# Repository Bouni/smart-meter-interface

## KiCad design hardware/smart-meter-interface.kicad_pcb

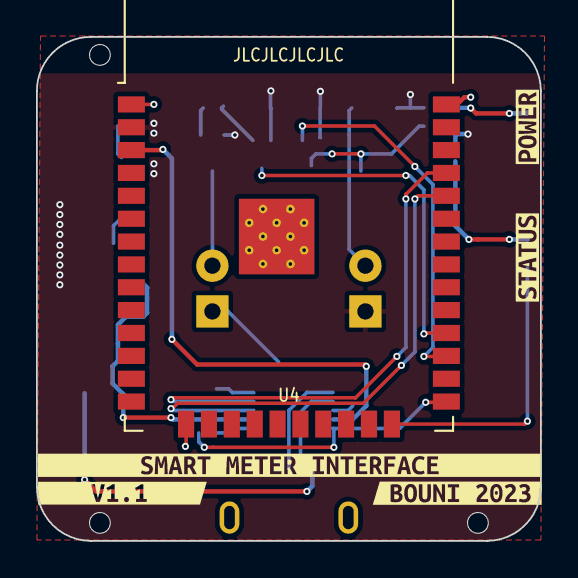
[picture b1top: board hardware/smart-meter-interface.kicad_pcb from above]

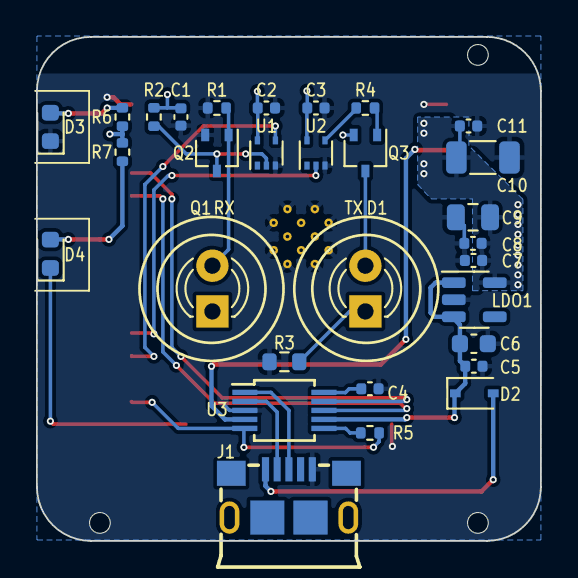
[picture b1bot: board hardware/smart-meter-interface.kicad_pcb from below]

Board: 2 copper layers, 28.0 x 28.0 mm, 39 parts (30 on the bottom side), 23 nets.

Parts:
C1, C2, C3, C5, C8, C11: 1uF; C_0402_1005Metric
C4, C7: 0.1uF; C_0402_1005Metric
C6: 10uF; C_0603_1608Metric
C9: 47uF; C_0805_2012Metric
C10: 100uF; C_1206_3216Metric
D1: SFH4356P; LED_D3.0mm_IRBlack
D2: 1N5819WS; D_SOD-323
D3: LED_G; LED_0603_1608Metric
D4: LED_B; LED_0603_1608Metric
J1: USB_B_Micro; MICRO-USB-SMD_10118193-0001LF
LDO1: ME6211C33M5G-N; SOT-23-5
Q1: SFH309; LED_D3.0mm_Clear
Q2: BC817W; SOT-323_SC-70
Q3: BC807W; SOT-323_SC-70
R1, R2, R4: 13K; R_0402_1005Metric
R3: 180; R_0603_1608Metric
R5: 4K7; R_0402_1005Metric
R6, R7: 1k; R_0402_1005Metric
TH: ToolingHole
TH#2, TH#3: ToolingHole
U1, U2: 74LVC1G17; SOT-553
U3: CH340X; MSOP-10_3x3mm_P0.5mm
U4: ESP32-WROOM-32
kibuzzard-651E74F7: G***; kibuzzard-651E74F7
kibuzzard-651E7500: G***; kibuzzard-651E7500
kibuzzard-651FCF74: G***; kibuzzard-651FCF74
kibuzzard-651FCFB8: G***; kibuzzard-651FCFB8
kibuzzard-651FCFC3: G***; kibuzzard-651FCFC3

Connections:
+3V3: C1.1, C2.1, C3.1, C7.1, C8.1, C9.1, C10.1, C11.1, LDO1.5 (VOUT), Q1.1 (C), Q3.2 (E), R2.1, R6.1, R7.1, U1.5 (VCC), U2.5 (VCC), U4.2 (VDD)
+5V: C5.1, C6.1, D2.1 (K), LDO1.1 (VIN), LDO1.3 (CE), U3.7 (VCC)
/D+: J1.3 (D+), U3.1 (UD+)
/D-: J1.2 (D-), U3.2 (UD-)
BLINK: U2.2, U4.28 (IO17)
EN: U3.4 (~RTS), U4.3 (EN)
GND: C1.2, C2.2, C3.2, C4.1, C5.2, C6.2, C7.2, C8.2, C9.2, C10.2, C11.2, D3.1 (K), J1.5 (GND), LDO1.2 (VSS), Q2.2 (E), R1.2, R3.2, U1.3 (GND), U2.3 (GND), U3.3 (GND), U4.1 (GND), U4.15 (GND), U4.38 (GND), U4.39 (GND)
IO0: R5.2, U3.5 (~CTS), U4.25 (IO0)
IO2: D4.1 (K), U4.24 (IO2)
unnamed: D1.2 (A), Q3.3 (C)
unnamed: D1.1 (K), R3.1
unnamed: D2.2 (A), J1.1 (VBUS)
unnamed: D3.2 (A), R6.2
unnamed: D4.2 (A), R7.2
unnamed: Q1.2 (E), Q2.1 (B), R1.1
unnamed: Q2.3 (C), R2.2, U1.2
unnamed: Q3.1 (B), R4.1
unnamed: R4.2, U2.4
unnamed: R5.1, U3.6 (TNOW/~DTR)
unnamed: C4.2, U3.10 (V3)
RX: U1.4, U4.27 (IO16)
RXD0: U3.8 (TXD), U4.34 (RXD0/IO3)
TXD0: U3.9 (RXD), U4.35 (TXD0/IO1)

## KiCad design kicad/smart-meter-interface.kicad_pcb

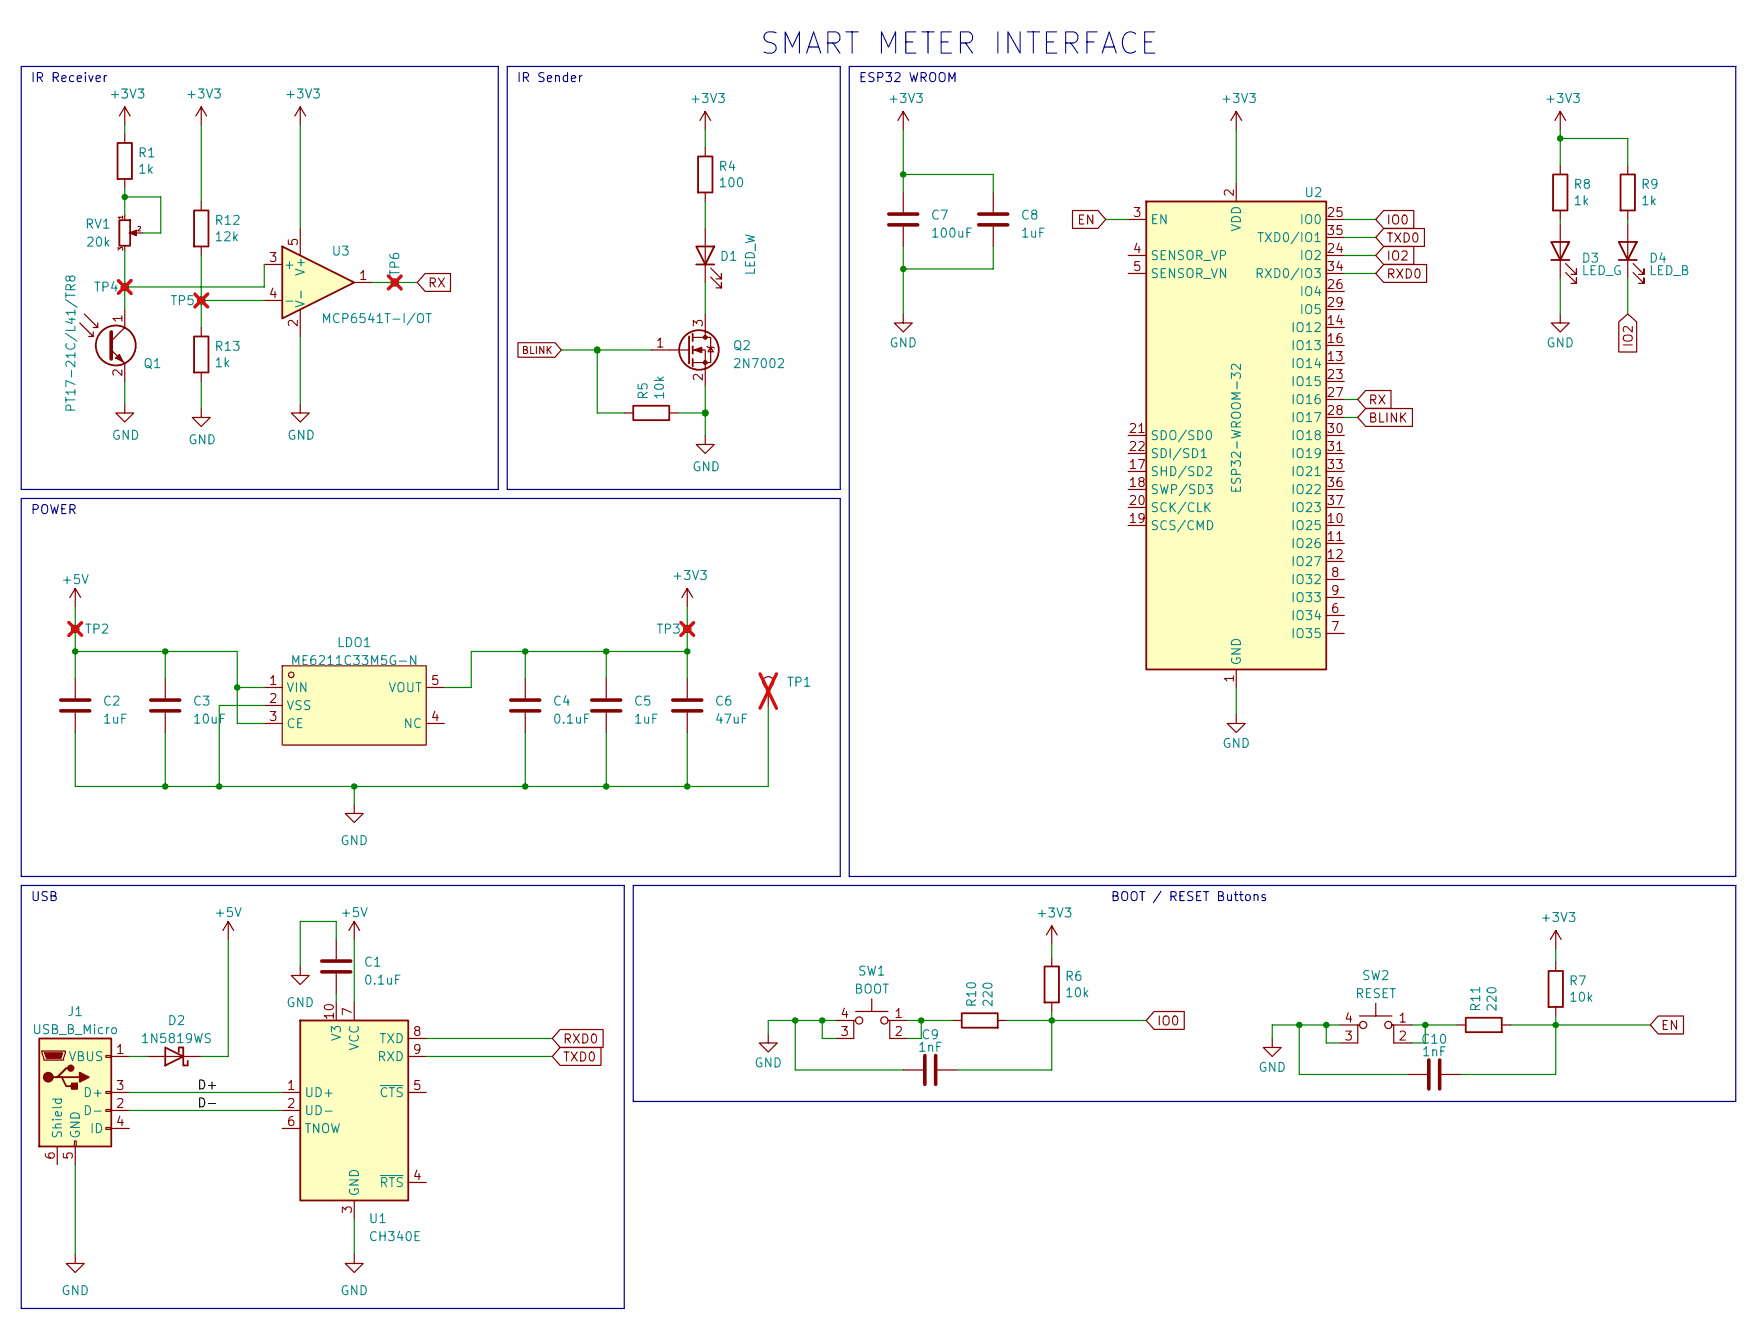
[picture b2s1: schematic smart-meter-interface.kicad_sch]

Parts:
C1, C4: 0.1uF; C_0402_1005Metric; LCSC C307331
C2, C5, C8: 1uF; C_0402_1005Metric; LCSC C52923
C3: 10uF; C_0603_1608Metric; LCSC C96446
C6: 47uF; C_0805_2012Metric; LCSC C16780
C7: 100uF; C_1206_3216Metric; LCSC C15008
C9, C10: 1nF; C_0402_1005Metric; LCSC C1523
D1: LED_W; LED_0805_2012Metric; LCSC C34499
D2: 1N5819WS; D_SOD-323; LCSC C191023
D3: LED_G; LED_0603_1608Metric; LCSC C72043
D4: LED_B; LED_0603_1608Metric; LCSC C72041
J1: USB_B_Micro; MICRO-USB-SMD_10118193-0001LF; LCSC C132562
LDO1: ME6211C33M5G-N; SOT-23-5_L3.0-W1.7-P0.95-LS2.8-BR; LCSC C82942
Q1: PT17-21C/L41/TR8; OPTO-SMD_L2.0-W1.3-R-FD; LCSC C100090
Q2: 2N7002; SOT-23; LCSC C8545
R1, R8, R9, R13: 1k; R_0402_1005Metric; LCSC C11702
R4: 100; R_0402_1005Metric; LCSC C25076
R5, R6, R7: 10k; R_0402_1005Metric; LCSC C25744
R10, R11: 220; R_0402_1005Metric; LCSC C25091
R12: 12k; R_0402_1005Metric; LCSC C25752
RV1: 20k; RES-ADJ-SMD_3P-L3.8-W3.0-P2.00-BL-FS; LCSC C128550
SW1: BOOT; SW-SMD_4P-L5.1-W5.1-P3.70-LS6.5-TL-2; LCSC C318884
SW2: RESET; SW-SMD_4P-L5.1-W5.1-P3.70-LS6.5-TL-2; LCSC C318884
TP1: TestPoint; TestPoint_Keystone_5000-5004_Miniature; not fitted
TP2, TP3, TP4, TP5, TP6: TestPoint_Small; TestPoint_Pad_D1.0mm; not fitted
U1: CH340E; MSOP-10_3x3mm_P0.5mm; LCSC C99652
U2: ESP32-WROOM-32
U3: MCP6541T-I/OT; SOT-23-5; LCSC C80839

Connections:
+3V3: C4.1, C5.1, C6.1, C7.1, C8.1, LDO1.5 (VOUT), R1.1, R4.1, R6.1, R7.1, R8.1, R9.1, R12.1, TP3.1, U2.2 (VDD), U3.5 (V+)
+5V: C2.1, C3.1, D2.1 (K), LDO1.1 (VIN), LDO1.3 (CE), TP2.1, U1.7 (VCC)
/D+: J1.3 (D+), U1.1 (UD+)
/D-: J1.2 (D-), U1.2 (UD-)
BLINK: Q2.1 (G), R5.1, U2.28 (IO17)
EN: C10.2, R7.2, R11.2, U2.3 (EN)
GND: C1.1, C2.2, C3.2, C4.2, C5.2, C6.2, C7.2, C8.2, C9.1, C10.1, D3.1 (K), J1.5 (GND), LDO1.2 (VSS), Q1.2 (E), Q2.2 (S), R5.2, R13.2, SW1.3 (K), SW1.4 (A), SW2.3 (K), SW2.4 (A), TP1.1, U1.3 (GND), U2.1 (GND), U2.15 (GND), U2.38 (GND), U2.39 (GND), U3.2 (V-)
IO0: C9.2, R6.2, R10.2, U2.25 (IO0)
IO2: D4.1 (K), U2.24 (IO2)
unnamed: D1.2 (A), R4.2
unnamed: D1.1 (K), Q2.3 (D)
unnamed: D2.2 (A), J1.1 (VBUS)
unnamed: D3.2 (A), R8.2
unnamed: D4.2 (A), R9.2
unnamed: Q1.1 (C), RV1.3, TP4.1, U3.3 (+)
unnamed: R1.2, RV1.1, RV1.2
unnamed: R10.1, SW1.1, SW1.2
unnamed: R11.1, SW2.1, SW2.2
unnamed: C1.2, U1.10 (V3)
unnamed: R12.2, R13.1, TP5.1, U3.4 (-)
RX: TP6.1, U2.27 (IO16), U3.1
RXD0: U1.8 (TXD), U2.34 (RXD0/IO3)
TXD0: U1.9 (RXD), U2.35 (TXD0/IO1)

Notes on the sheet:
POWER
USB
BOOT / RESET Buttons
ESP32 WROOM
SMART METER INTERFACE
IR Sender
IR Receiver

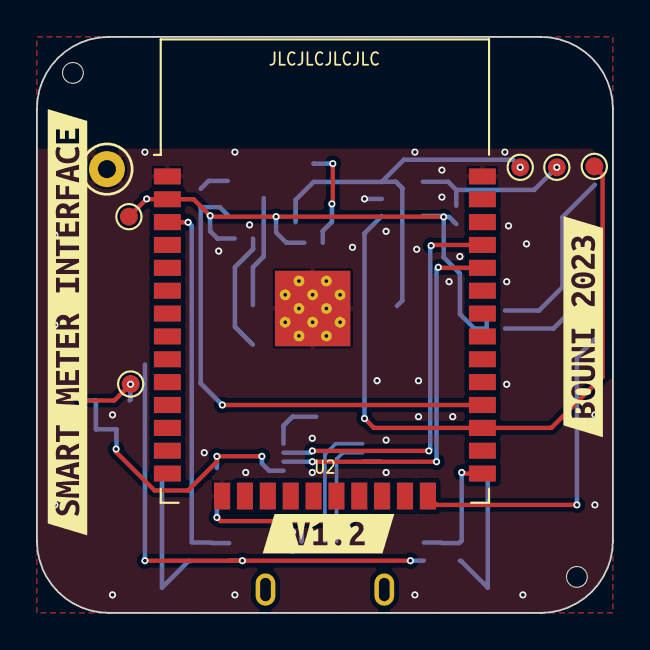
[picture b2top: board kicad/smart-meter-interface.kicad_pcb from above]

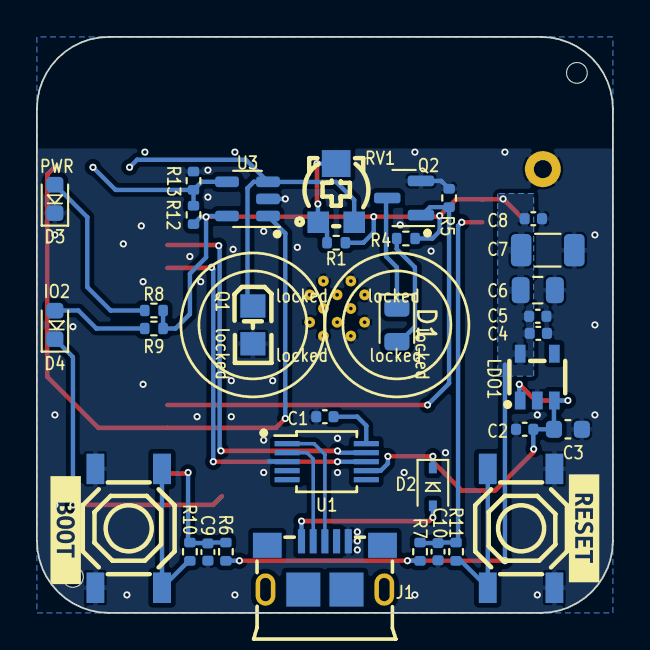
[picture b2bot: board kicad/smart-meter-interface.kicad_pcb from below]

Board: 2 copper layers, 32.0 x 32.0 mm, 48 parts (36 on the bottom side), 23 nets.

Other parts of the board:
TH1, TH2: ToolingHole
kibuzzard-63C57836: G***; kibuzzard-63C57836
kibuzzard-635BBB2F: G***; kibuzzard-635BBB2F
kibuzzard-635BBB9A: G***; kibuzzard-635BBB9A
kibuzzard-635BBBA9: G***; kibuzzard-635BBBA9
kibuzzard-64709697: G***; kibuzzard-64709697

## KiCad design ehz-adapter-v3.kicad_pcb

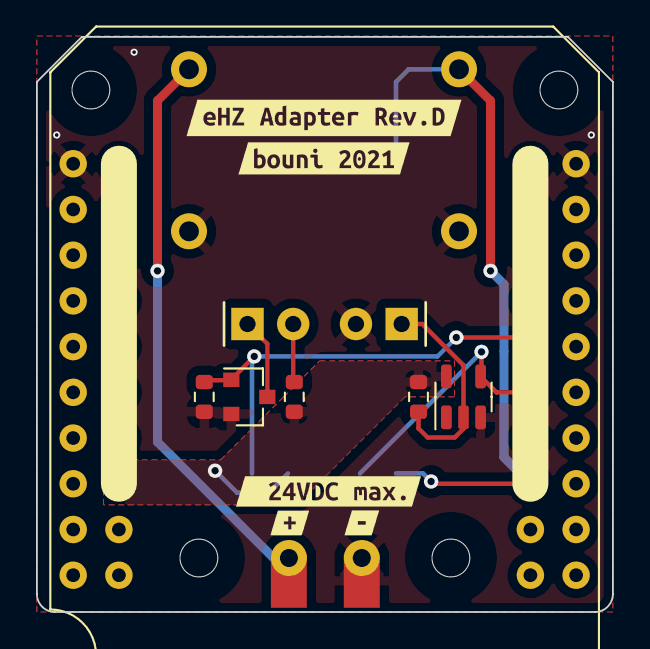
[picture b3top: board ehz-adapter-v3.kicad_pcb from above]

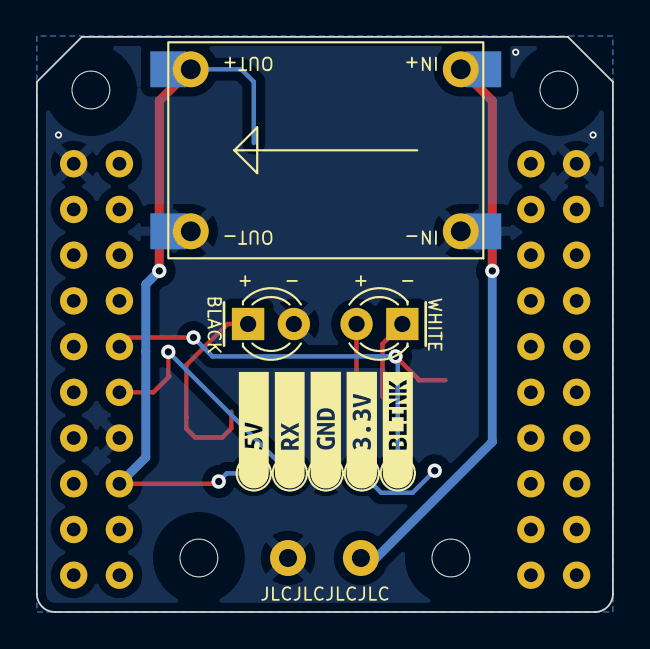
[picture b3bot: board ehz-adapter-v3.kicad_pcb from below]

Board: 2 copper layers, 32.0 x 32.0 mm, 30 parts (13 on the bottom side), 9 nets.

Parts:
D1: LTE-4206; LED_D3.0mm_Clear
H1, H2, H3, H4: MountingHole; MountingHole_2.1mm
J1, J2: Conn_01x01_Female; Power-tap
Q1: SFH 309 FA-5/6; LED_D3.0mm_IRBlack
Q2: AO3400A; SOT-23
R1, R5: 10k; R_0603_1608Metric
R4: 100; R_0603_1608Metric
TP1, TP2, TP4, TP5, TP6: TestPoint; TestPoint_Pad_D1.5mm
U1: mh-et-live-minikit; MH-ET LIVE MiniKit
U2: DC-DC-BOARD; DC-DC-MODULE
U3: 74LVC1G17DBVR; SOT-23-5
kibuzzard-61B75BD6: G***; kibuzzard-61B75BD6
kibuzzard-61B75BED: G***; kibuzzard-61B75BED
kibuzzard-61B75BFD: G***; kibuzzard-61B75BFD
kibuzzard-61B75C18: G***; kibuzzard-61B75C18
kibuzzard-61F2A0D7: G***; kibuzzard-61F2A0D7
kibuzzard-61F1756A: G***; kibuzzard-61F1756A
kibuzzard-61F17555: G***; kibuzzard-61F17555
kibuzzard-61F17572: G***; kibuzzard-61F17572
kibuzzard-61F17596: G***; kibuzzard-61F17596
kibuzzard-61F23799: G***; kibuzzard-61F23799

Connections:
+3V3: R1.1, R4.1, TP4.1, U1.18 (3V3), U3.5 (VCC)
+5V: TP2.1, U1.28 (5V), U2.3 (OUT+)
/24V: J1.1, U2.2 (IN+)
BLINK: Q2.1 (G), R5.1, TP6.1, U1.25 (IO17)
GND: J2.1, Q1.2 (E), Q2.2 (S), R5.2, TP1.1, U1.1 (GND), U1.27 (GND), U1.31 (GND), U2.1 (IN-), U2.4 (OUT-), U3.3 (GND)
unnamed: D1.2 (A), R4.2
unnamed: D1.1 (K), Q2.3 (D)
unnamed: Q1.1 (C), R1.2, U3.2
RX: TP5.1, U1.26 (IO16), U3.4

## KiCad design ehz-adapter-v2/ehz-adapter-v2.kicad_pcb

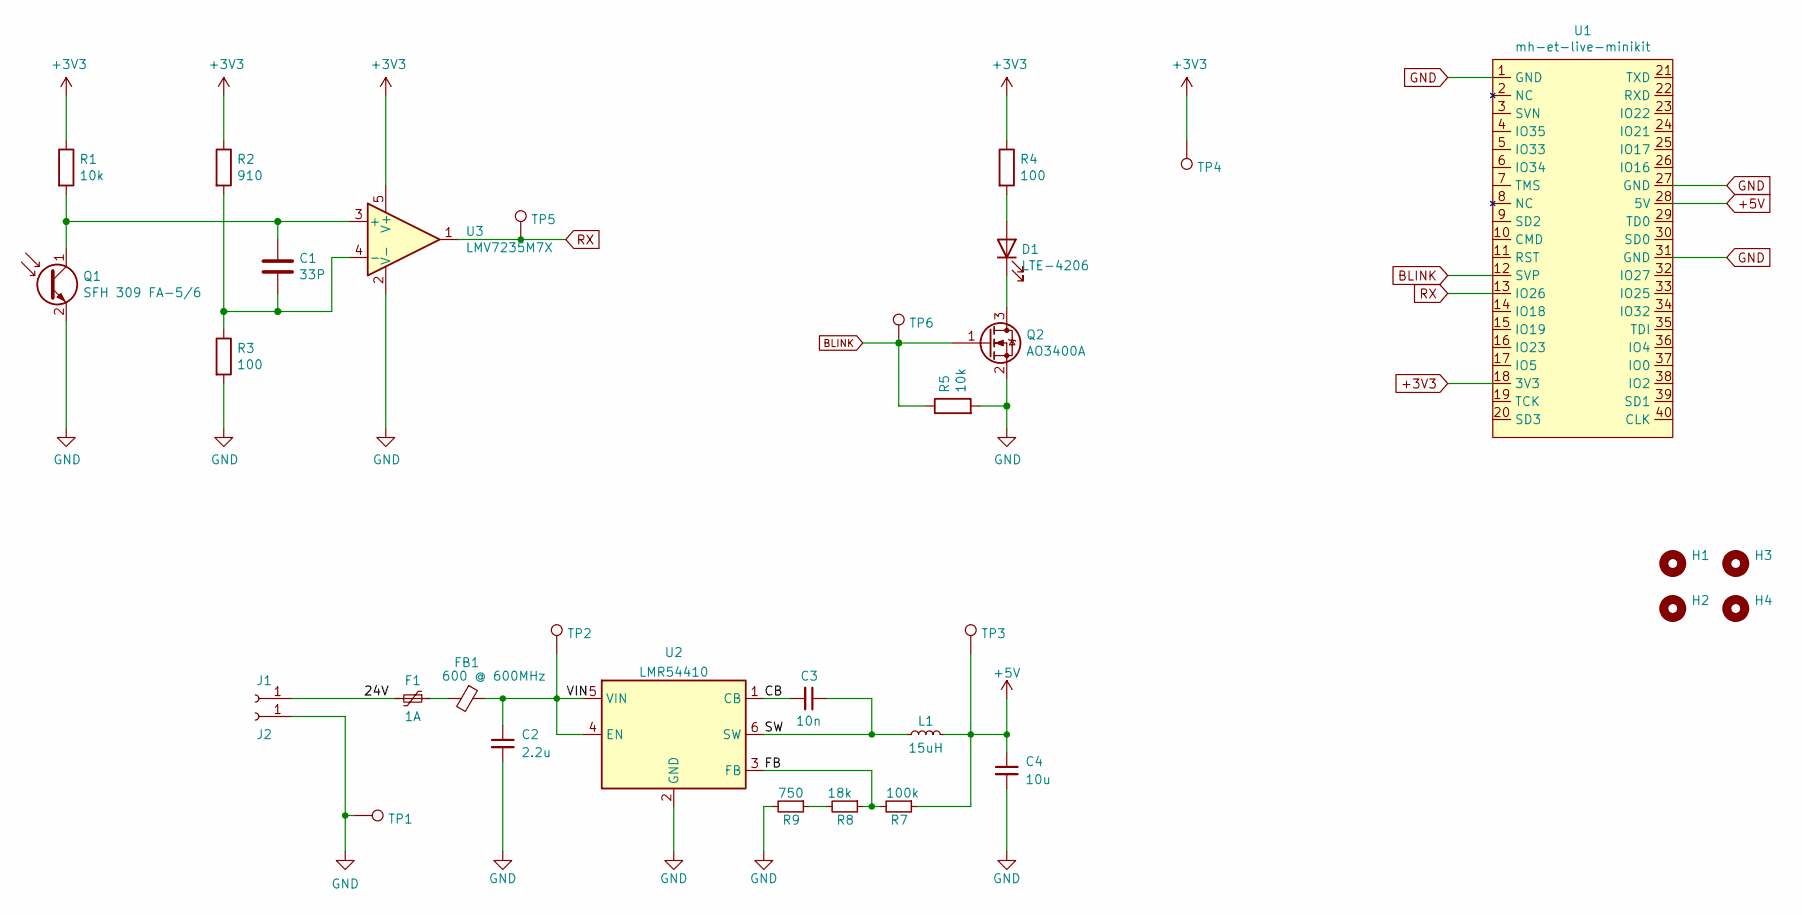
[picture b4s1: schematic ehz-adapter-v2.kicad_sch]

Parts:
C1: 33P; C_0603_1608Metric; LCSC C1663
C2: 2.2u; C_1206_3216Metric; LCSC Part # C50254
C3: 10n; C_0603_1608Metric; LCSC Part # C57112
C4: 10u; C_0603_1608Metric; LCSC Part # C19702
D1: LTE-4206; LED_D3.0mm_Clear
F1: 1A; Fuse_1206_3216Metric; LCSC Part # C369159
FB1: 600 @ 600MHz; L_0805_2012Metric; LCSC Part # C1017
H1, H2, H3, H4: MountingHole; MountingHole_2.1mm
J1, J2: Conn_01x01_Female; Pin_D1.0mm_L10.0mm
L1: 15uH; L_Sumida_CDMC6D28_7.25x6.5mm; LCSC Part # C182182
Q1: SFH 309 FA-5/6; LED_D3.0mm_IRBlack
Q2: AO3400A; SOT-23; LCSC C20917
R1, R5: 10k; R_0603_1608Metric; LCSC C25804
R2: 910; R_0603_1608Metric; LCSC C23264
R3, R4: 100; R_0603_1608Metric; LCSC C22775
R7: 100k; R_0603_1608Metric; LCSC Part # C25803
R8: 18k; R_0603_1608Metric; LCSC Part # C25810
R9: 750; R_0603_1608Metric; LCSC Part # C23241
TP1, TP2, TP3, TP4, TP5, TP6: TestPoint; TestPoint_Pad_D1.5mm
U1: mh-et-live-minikit; MH-ET LIVE MiniKit
U2: LMR54410; SOT-23-6
U3: LMV7235M7X; SOT-353_SC-70-5; LCSC C202268

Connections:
+3V3: R1.1, R2.1, R4.1, TP4.1, U1.18 (3V3), U3.5 (V+)
+5V: C4.1, L1.2, R7.1, TP3.1, U1.28 (5V)
/24V: F1.2, J1.1
/CB: C3.2, U2.1 (CB)
/FB: R7.2, R8.1, U2.3 (FB)
/SW: C3.1, L1.1, U2.6 (SW)
/VIN: C2.1, FB1.1, TP2.1, U2.4 (EN), U2.5 (VIN)
BLINK: Q2.1 (G), R5.1, TP6.1, U1.12 (SVP)
GND: C2.2, C4.2, J2.1, Q1.2 (E), Q2.2 (S), R3.2, R5.2, R9.2, TP1.1, U1.1 (GND), U1.27 (GND), U1.31 (GND), U2.2 (GND), U3.2 (V-)
unnamed: C1.1, Q1.1 (C), R1.2, U3.3 (+)
unnamed: C1.2, R2.2, R3.1, U3.4 (-)
unnamed: D1.1 (K), Q2.3 (D)
unnamed: D1.2 (A), R4.2
unnamed: F1.1, FB1.2
unnamed: R8.2, R9.1
RX: TP5.1, U1.13 (IO26), U3.1

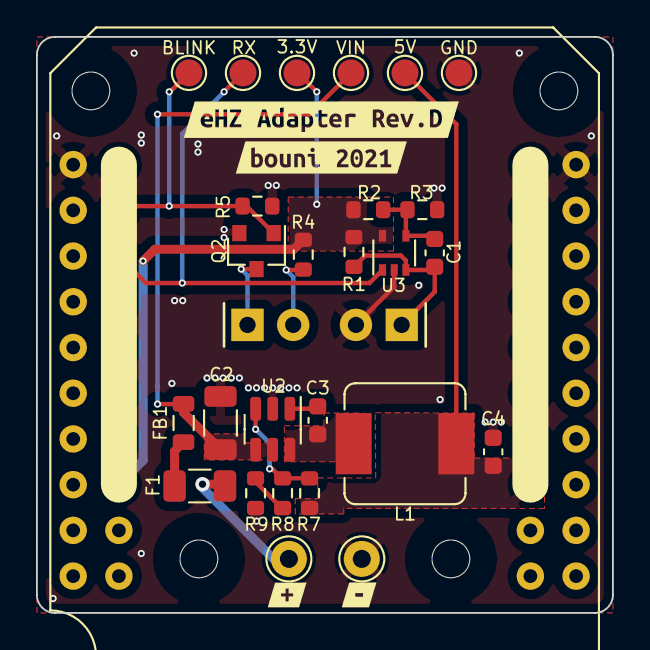
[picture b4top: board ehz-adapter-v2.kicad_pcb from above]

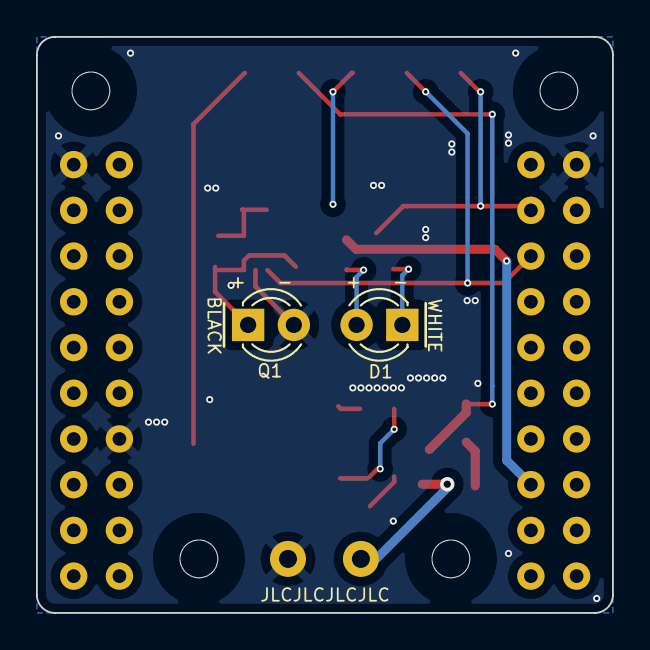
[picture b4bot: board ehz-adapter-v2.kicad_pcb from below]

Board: 2 copper layers, 32.0 x 32.0 mm, 37 parts (2 on the bottom side), 16 nets.

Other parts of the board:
kibuzzard-61B75BD6: G***; kibuzzard-61B75BD6
kibuzzard-61B75BED: G***; kibuzzard-61B75BED
kibuzzard-61B75BFD: G***; kibuzzard-61B75BFD
kibuzzard-61B75C18: G***; kibuzzard-61B75C18

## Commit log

2020-10-07 Alpha stage prototype
2020-10-08 moved mounting hooles
2021-02-18 fixed major layout fuckup, added MH-ET-LIVE-minikit footprint and symbol
2021-02-18 add gitignore
2021-02-18 no longer track kicad_prl file
2021-02-19 fixed wrong comperator footprint, added alternative power pads
2021-02-19 replaced custom power connector pads
2021-02-19 removed useless pictures and greber files
2021-02-19 removed backup file
2021-02-19 added datasheets, removed duplicate step file
2021-02-21 last minor fixes before ordering at JLCPCB
2021-12-13 Replaced D-SUN with custom Buck converter
2021-12-21 added custom buck converter
2022-09-30 current state, works, no idea what changed
2022-10-24 Many changes to use ESP32 WROOM
2022-10-24 extended gitignore
2022-10-31 almost finished refactor
2022-10-31 replaced .wrl with .step for all possible 3D models
2022-11-04 Replaced USB micro connector 3d Model with Step file
2022-11-23 Refactor to use Comperator instead of Schmitt Trigger
2022-11-24 Final adjustments, next prototypes are ordered
2022-12-30 Major cleanup, hopefully working prototype orderd
2022-12-30 Fixed last issues
2023-01-06 Fixed wrong LCSC number of R1
2023-01-12 cleanup 3d model paths
2023-01-12 Add 3D images
2023-01-12 moved kicad design files into subfolder
2023-01-12 Add first ESPHome config attempt
2023-01-12 fixed yaml -> yaml tipo
2023-01-12 Add second meter
2023-01-12 add secrets.yaml example
2023-01-13 Finished tests, seems to work on my test meter
2023-01-14 fixed disconnects caused by publik key sensor
2023-01-16 Minor cleanups for V1.1
2023-10-03 Don't know what changed, something minor for sure
2023-10-05 completely refactored to CH340X and Volkszähler IR circuit
2023-10-05 shrinked pcb further to 28x28mm
2023-10-06 Minor improvements
2023-10-06 Streamlined annotations
2023-10-06 Updated pictures
2023-10-18 Step generiert
